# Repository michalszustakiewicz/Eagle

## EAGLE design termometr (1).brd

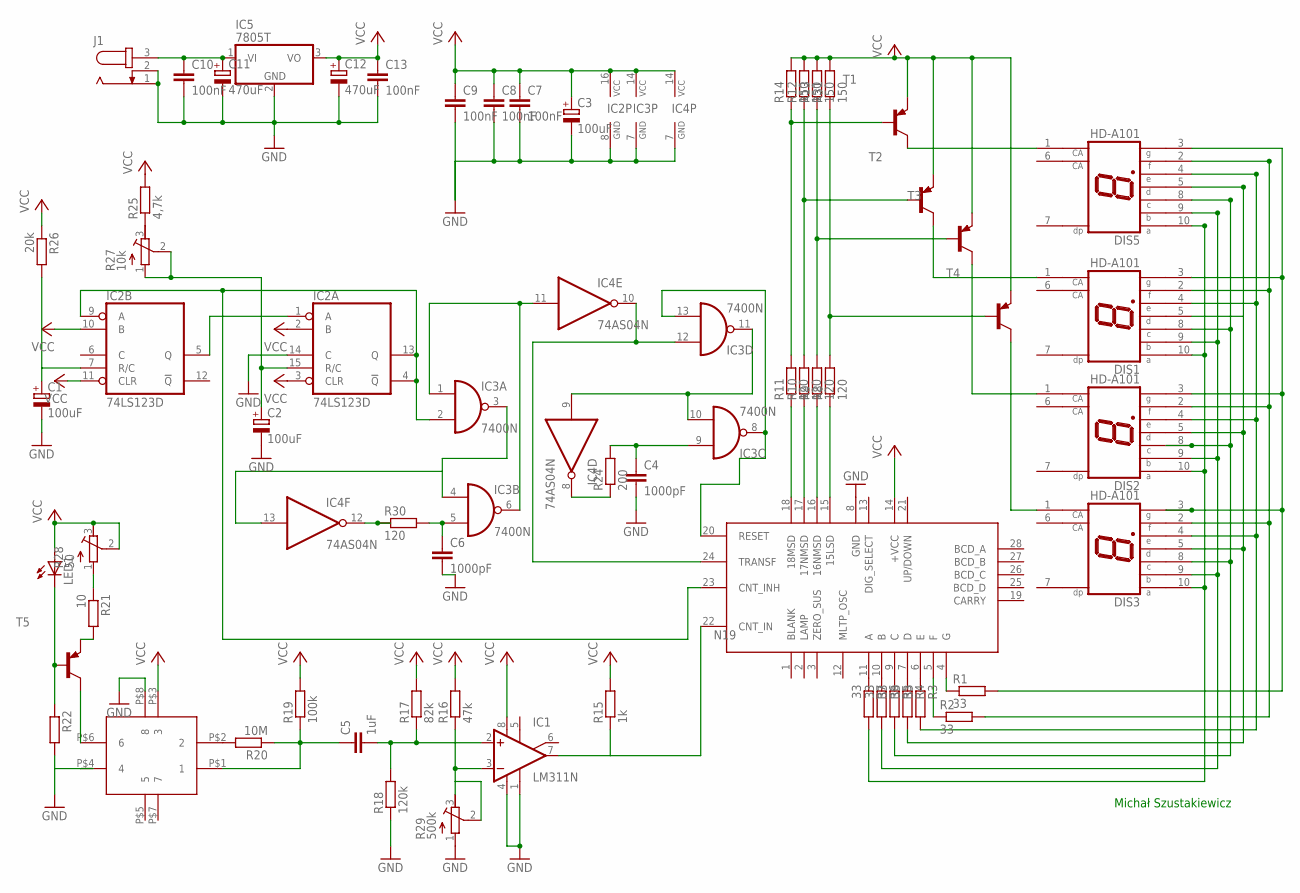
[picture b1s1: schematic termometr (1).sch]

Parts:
C1, C2, C3: 100uF; E2,5-5
C4, C6: 1000pF; C1206
C5: 1uF; C1206
C7, C8, C9, C10, C13: 100nF; C1206
C11, C12: 470uF; E2,5-5
DIS1, DIS2, DIS3, DIS5: HD-A101; HDSP-A
IC1: LM311N; DIL08
IC2: 74LS123D; SO16
IC3: 7400N; DIL14
IC4: 74AS04N; DIL14
IC5: 7805T; TO220H
J1: JACK-PLUG0; SPC4077
LED1: LED5MM
R1, R2, R3, R4, R5, R6, R7: 33; M1206
R8, R9, R10, R11, R30: 120; M1206
R12, R13, R14, R31: 150; M1206
R15: 1k; M1206
R16: 47k; M1206
R17: 82k; M1206
R18: 120k; M1206
R19: 100k; M1206
R20: 10M; M1206
R21: 10; M1206
R22: R-EU_M1206; M1206
R24: 200; M1206
R25: 4,7k; M1206
R26: 20k; M1206
R27: 10k; RTRIM3202
R28: 50; RTRIM3202
R29: 500k; RTRIM3202
T1, T2, T3, T4, T5: 2N3906-PNP-TO92-EBC; TO92-EBC
U$1: ZN1040E
U$2: HEDS_1200

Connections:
15: R8.2, R31.1, T4.B
16: R9.2, R13.1, T3.B
17: R10.2, R12.1, T2.B
18: R11.2, R14.1, T1.B
GND: C1.-, C2.-, C3.-, C4.2, C6.2, C7.2, C8.2, C9.2, C10.2, C11.-, C12.-, C13.2, IC1.1 (GND), IC1.4 (V-), IC2.8 (GND), IC2.14 (C), IC3.7 (GND), IC4.7 (GND), IC5.2 (GND), J1.1, J1.2, R18.1, R22.2, R29.1 (A), U$1.8 (GND), U$2.P$4 (4), U$2.P$8 (8)
N19: IC2.4 (!Q), IC2.9 (A), IC2.13 (Q), IC3.2 (I1), U$1.23 (CNT_INH)
unnamed: IC3.10 (I1), IC3.11 (O), IC4.9 (I)
unnamed: LED1.K (C), R22.1, T5.B
unnamed: C1.+, IC2.7 (R/C), R26.2
unnamed: R21.1, R28.1 (A)
unnamed: R21.2, T5.E
unnamed: C5.2, IC1.2 (+IN), R17.1, R18.2
unnamed: IC1.3 (-IN), R16.1, R29.2 (S), R29.3 (E)
unnamed: C5.1, R19.1, R20.1, U$2.P$1 (1)
unnamed: R20.2, U$2.P$2 (2)
unnamed: IC1.7 (OUT), R15.1, U$1.22 (CNT_IN)
unnamed: C6.1, IC3.5 (I1), R30.2
unnamed: IC4.12 (O), R30.1
unnamed: C4.1, IC3.9 (I0), R24.2
unnamed: IC4.8 (O), R24.1
unnamed: C10.1, C11.+, IC5.1 (VI), J1.3
unnamed: IC3.1 (I0), IC3.6 (O), IC4.11 (I)
unnamed: IC3.12 (I0), IC4.10 (O), U$1.24 (TRANSF)
unnamed: DIS1.10 (A), DIS2.10 (A), DIS3.10 (A), DIS5.10 (A), R7.2
unnamed: R1.1, U$1.4 (G)
unnamed: C2.+, IC2.15 (R/C), R27.1 (A), R27.2 (S)
unnamed: R25.1, R27.3 (E)
unnamed: DIS1.9 (B), DIS2.9 (B), DIS3.9 (B), DIS5.9 (B), R6.2
unnamed: R2.1, U$1.5 (F)
unnamed: IC3.3 (O), IC3.4 (I0), IC4.13 (I)
unnamed: IC2.1 (A), IC2.5 (Q)
unnamed: T5.C, U$2.P$6 (6)
unnamed: R3.1, U$1.6 (E)
unnamed: R4.1, U$1.7 (D)
unnamed: R5.1, U$1.9 (C)
unnamed: R6.1, U$1.10 (B)
unnamed: R7.1, U$1.11 (A)
unnamed: R11.1, U$1.18 (18MSD)
unnamed: R10.1, U$1.17 (17NMSD)
unnamed: R9.1, U$1.16 (16NMSD)
unnamed: R8.1, U$1.15 (15LSD)
unnamed: DIS1.8 (C), DIS2.8 (C), DIS3.8 (C), DIS5.8 (C), R5.2
unnamed: DIS1.5 (D), DIS2.5 (D), DIS3.5 (D), DIS5.5 (D), R4.2
unnamed: DIS1.4 (E), DIS2.4 (E), DIS3.4 (E), DIS5.4 (E), R3.2
unnamed: DIS1.2 (F), DIS2.2 (F), DIS3.2 (F), DIS5.2 (F), R2.2
unnamed: DIS1.3 (G), DIS2.3 (G), DIS3.3 (G), DIS5.3 (G), R1.2
unnamed: DIS3.1 (CA), T4.C
unnamed: DIS2.1 (CA), T3.C
unnamed: DIS1.1 (CA), T2.C
unnamed: DIS5.1 (CA), T1.C
RESET: IC3.8 (O), IC3.13 (I1), U$1.20 (RESET)
VCC: C3.+, C7.1, C8.1, C9.1, C12.+, C13.1, IC1.8 (V+), IC2.2 (B), IC2.3 (CLR), IC2.10 (B), IC2.11 (CLR), IC2.16 (VCC), IC3.14 (VCC), IC4.14 (VCC), IC5.3 (VO), LED1.A, R12.2, R13.2, R14.2, R15.2, R16.2, R17.2, R19.2, R25.2, R26.1, R28.2 (S), R28.3 (E), R31.2, T1.E, T2.E, T3.E, T4.E, U$1.14 (+VCC), U$2.P$3 (3)

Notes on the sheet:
Michał Szustakiewicz

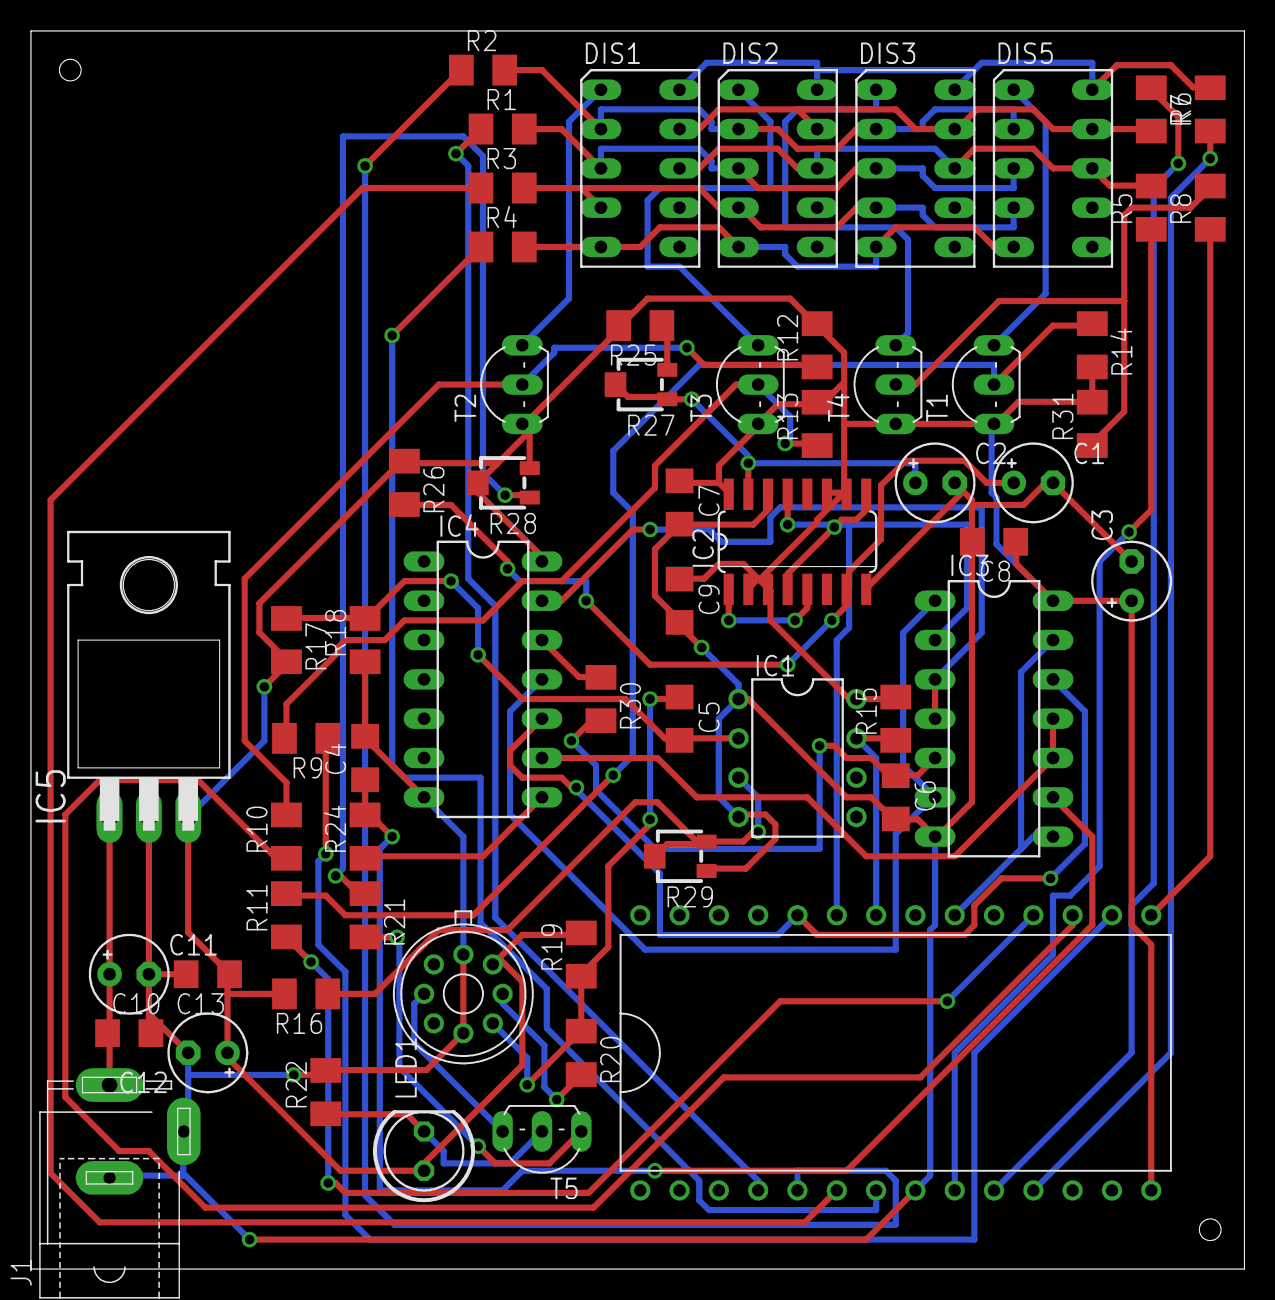
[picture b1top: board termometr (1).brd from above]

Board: 2 copper layers, 78.4 x 80.0 mm, 61 parts (0 on the bottom side), 52 nets.

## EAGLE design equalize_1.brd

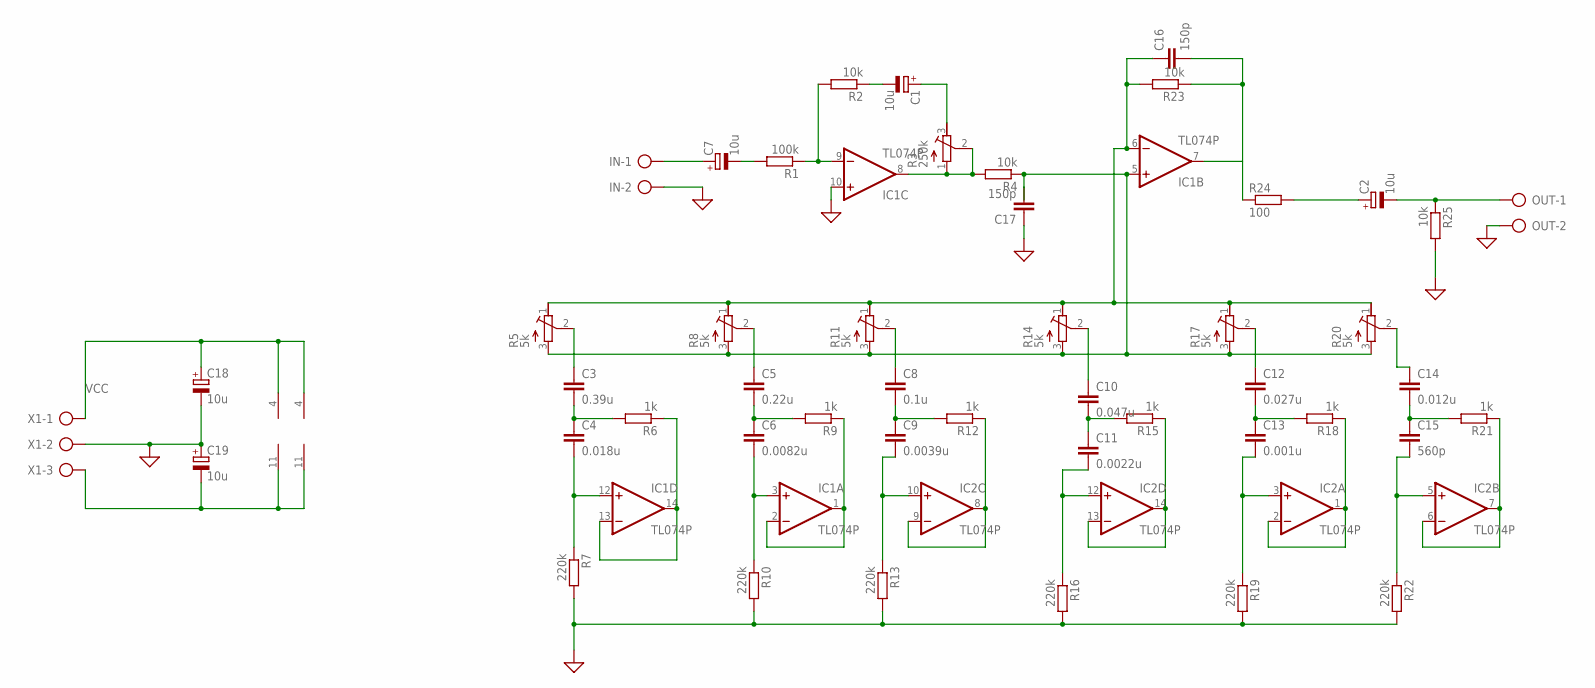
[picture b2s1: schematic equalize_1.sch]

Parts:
C1, C2, C7, C18, C19: 10u; E2,5-5
C3: 0.39u; C0603
C4: 0.018u; C0603
C5: 0.22u; C0603
C6: 0.0082u; C0603
C8: 0.1u; C0603
C9: 0.0039u; C0603
C10: 0.047u; C0603
C11: 0.0022u; C0603
C12: 0.027u; C0603
C13: 0.001u; C0603
C14: 0.012u; C0603
C15: 560p; C0603
C16, C17: 150p; C0603
IC1, IC2: TL074P; DIL14
IN: AK500/2
OUT: AK500/2
R1: 100k; 0207/7
R2, R4, R23, R25: 10k; 0207/7
R3: 250k; RTRIM3339P
R5, R8, R11, R14, R17, R20: 5k; RTRIMT93YA
R6, R9, R12, R15, R18, R21: 1k; 0207/7
R7, R10, R13, R16, R19, R22: 220k; 0207/7
R24: 100; 0207/7
X1: AK500/3

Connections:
GND: C17.1, C18.-, C19.+, IC1.10 (+IN), IN.2, OUT.2, R7.2, R10.2, R13.2, R16.2, R19.2, R22.2, R25.2, X1.2
IN: C7.+, IN.1
unnamed: C1.-, R2.1
unnamed: C1.+, R3.3 (E)
unnamed: IC1.8 (OUT), R3.1 (A), R3.2 (S), R4.2
unnamed: C19.-, IC1.11 (V-), IC2.11 (V-), X1.3
unnamed: C16.2, IC1.7 (OUT), R23.1, R24.1
unnamed: C2.+, R24.2
unnamed: C16.1, IC1.6 (-IN), R5.1 (E), R8.1 (E), R11.1 (E), R14.1 (E), R17.1 (E), R20.1 (E), R23.2
unnamed: IC1.9 (-IN), R1.1, R2.2
unnamed: C7.-, R1.2
unnamed: C17.2, IC1.5 (+IN), R4.1, R5.3 (A), R8.3 (A), R11.3 (A), R14.3 (A), R17.3 (A), R20.3 (A)
unnamed: C3.1, R5.2 (S)
unnamed: C3.2, C4.1, R6.2
unnamed: IC1.13 (-IN), IC1.14 (OUT), R6.1
unnamed: C4.2, IC1.12 (+IN), R7.1
unnamed: C5.1, R8.2 (S)
unnamed: C5.2, C6.1, R9.2
unnamed: IC1.1 (OUT), IC1.2 (-IN), R9.1
unnamed: C6.2, IC1.3 (+IN), R10.1
unnamed: C8.1, R11.2 (S)
unnamed: C8.2, C9.1, R12.2
unnamed: IC2.8 (OUT), IC2.9 (-IN), R12.1
unnamed: C9.2, IC2.10 (+IN), R13.1
unnamed: C10.1, R14.2 (S)
unnamed: C10.2, C11.1, R15.2
unnamed: IC2.13 (-IN), IC2.14 (OUT), R15.1
unnamed: C11.2, IC2.12 (+IN), R16.1
unnamed: C12.1, R17.2 (S)
unnamed: C12.2, C13.1, R18.2
unnamed: IC2.1 (OUT), IC2.2 (-IN), R18.1
unnamed: C13.2, IC2.3 (+IN), R19.1
unnamed: C14.1, R20.2 (S)
unnamed: C14.2, C15.1, R21.2
unnamed: IC2.6 (-IN), IC2.7 (OUT), R21.1
unnamed: C15.2, IC2.5 (+IN), R22.1
OUT: C2.-, OUT.1, R25.1
VCC: C18.+, IC1.4 (V+), IC2.4 (V+), X1.1

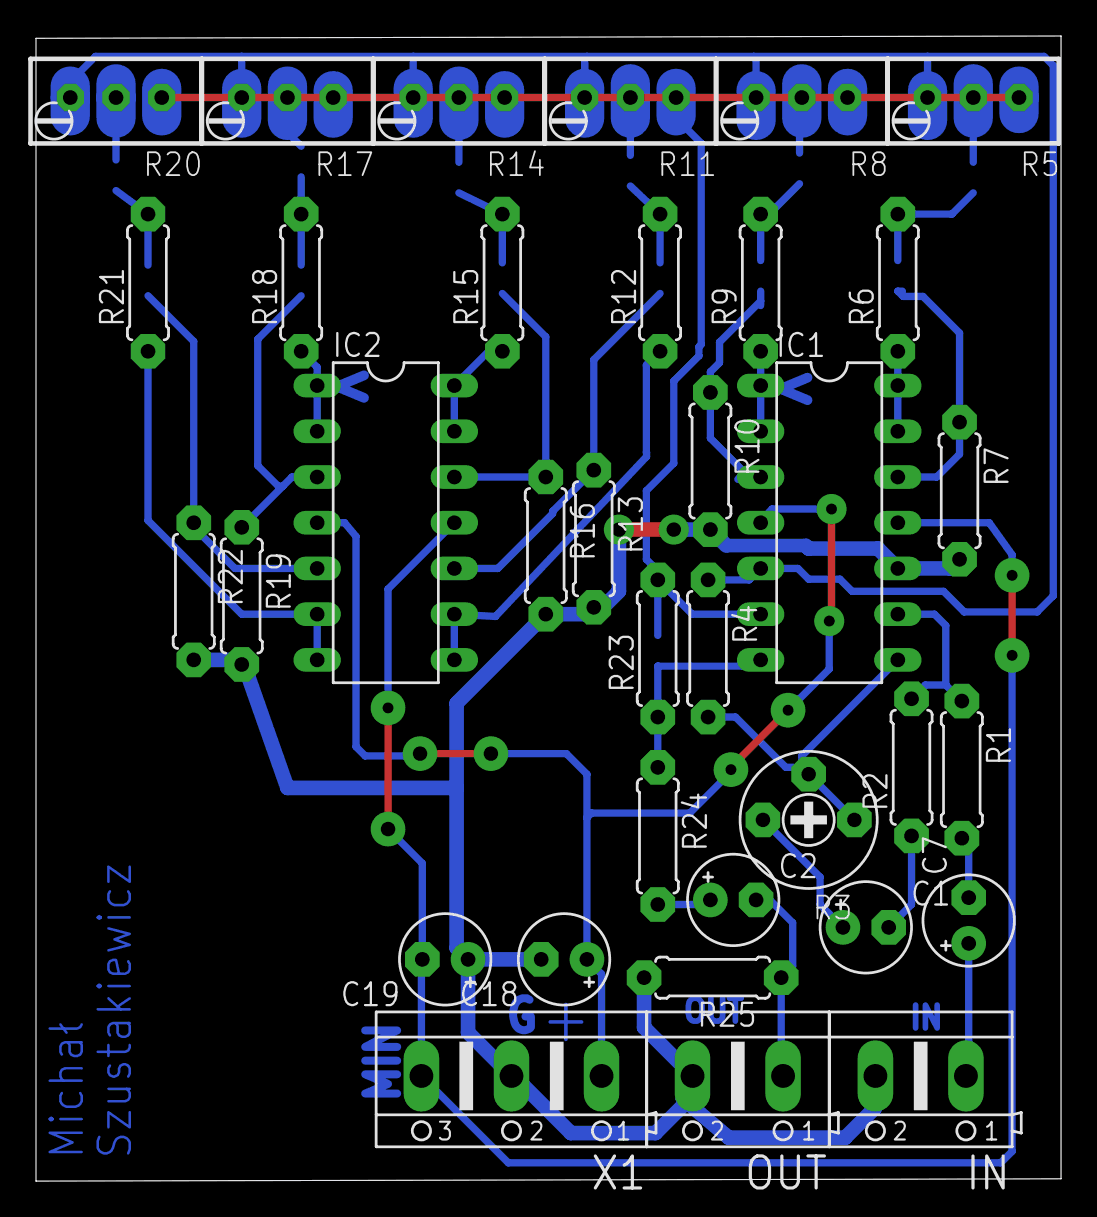
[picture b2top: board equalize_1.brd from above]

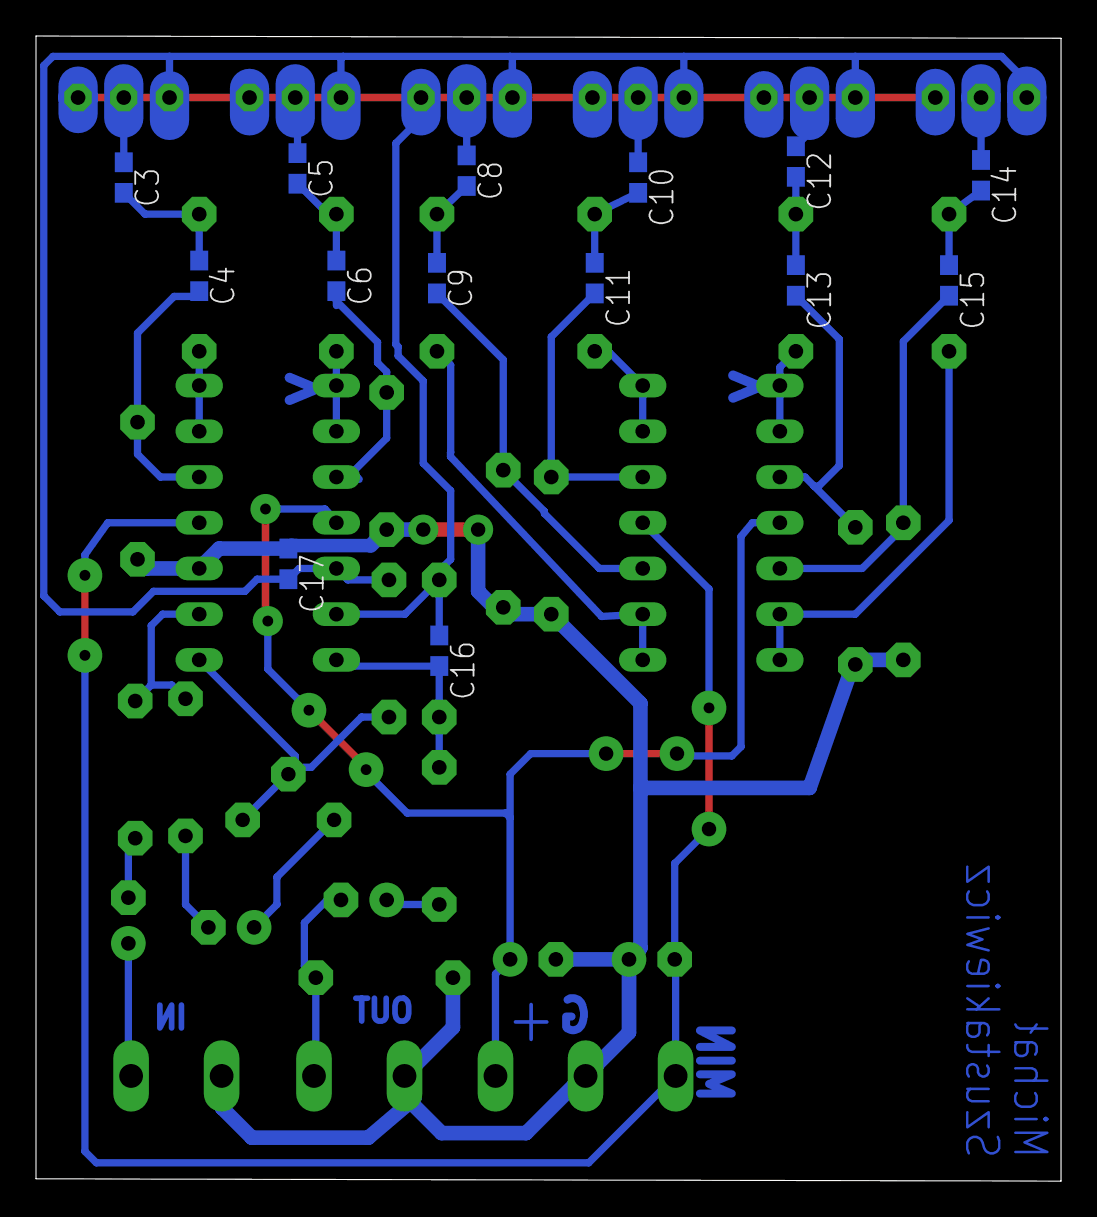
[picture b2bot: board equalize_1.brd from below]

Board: 2 copper layers, 56.9 x 63.6 mm, 49 parts (14 on the bottom side), 38 nets.
